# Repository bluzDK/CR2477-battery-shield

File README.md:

Bluz CR2477 Battery Shield Hardware Files
==========
Bluz is a Development Kit (DK) that implements the Wiring language and talks to the [Particle](https://www.particle.io/) cloud through Bluetooth Low Energy. It can be accessed through a REST API and programmed from a Web IDE.

The CR2477 battery shield is intended to let bluz run off the biggest, baddest coin cell battery in the land.

This shield is not produced or sold, the files are provided here as a reference or so others can create the shield themselves. The PCB can be purchased from [OSH Park directly here](https://oshpark.com/shared_projects/7VCoguxF). The BOM has all the parts listed with links to DigiKey for easy purchase. 

These files have been made available online through a [Creative Commons Attribution-ShareAlike 3.0](http://creativecommons.org/licenses/by-sa/3.0/) license.

You are welcome to distribute, remix, and use these files for commercial purposes. If you do so, please attribute the original design to Bluz both on the website and on the physical packaging of the product or in the instruction manual. All derivative works must be published under the same or a similar license.

All items are subject to change over time as the product is designed, so make sure you are always looking at the latest information by pulling often.

##Sections
<b>BOM</b>: Current Bill of Materials for the battery shield.

<b>HW Design</b>: Schematics, board layouts, and other design files.

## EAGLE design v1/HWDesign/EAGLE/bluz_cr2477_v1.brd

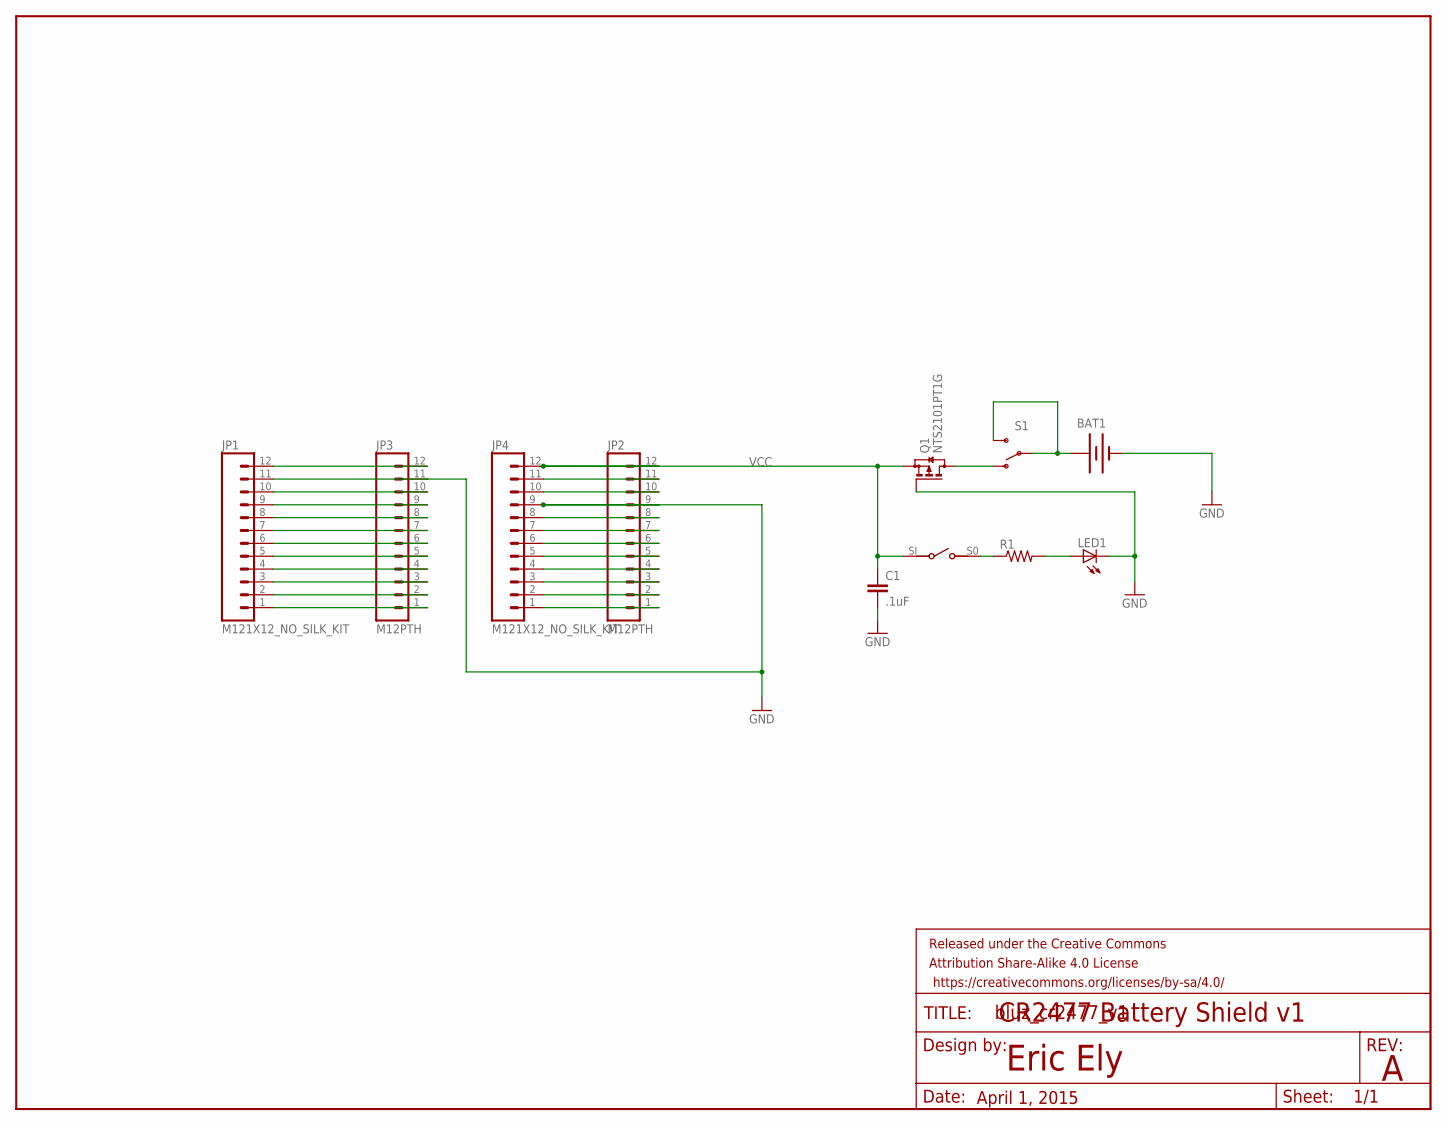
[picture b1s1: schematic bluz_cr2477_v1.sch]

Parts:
BAT1: BATTERY245PTH; BATTCON_245MM_PTH
C1: .1uF; 0603-CAP
FRAME1: FRAME-LETTER; CREATIVE_COMMONS
JP1, JP4: M121X12_NO_SILK_KIT; 1X12_NO_SILK_KIT
JP2, JP3: M12PTH; 1X12
LED1: LEDCHIPLED_0603; CHIPLED_0603
Q1: NTS2101PT1G; SOT323
R1: RESISTOR0603-RES; 0603-RES
S1: SWITCH-SPDTKIT; SWITCH-SPDT_KIT
S2: CHS-01TASMD; CHS-01TA

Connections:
GND: BAT1.2 (-), C1.2, JP1.11, JP2.9, JP3.11, JP4.9, LED1.C, Q1.1 (G)
unnamed: BAT1.3 (+), S1.2, S1.3 (S)
unnamed: JP1.1, JP3.1
unnamed: LED1.A, R1.2
unnamed: R1.1, S2.S0 (SO)
unnamed: Q1.3 (D), S1.1 (O)
unnamed: JP1.2, JP3.2
unnamed: JP1.3, JP3.3
unnamed: JP1.4, JP3.4
unnamed: JP1.5, JP3.5
unnamed: JP1.6, JP3.6
unnamed: JP1.7, JP3.7
unnamed: JP1.8, JP3.8
unnamed: JP1.9, JP3.9
unnamed: JP1.10, JP3.10
unnamed: JP1.12, JP3.12
unnamed: JP2.1, JP4.1
unnamed: JP2.2, JP4.2
unnamed: JP2.3, JP4.3
unnamed: JP2.4, JP4.4
unnamed: JP2.5, JP4.5
unnamed: JP2.6, JP4.6
unnamed: JP2.7, JP4.7
unnamed: JP2.8, JP4.8
unnamed: JP2.10, JP4.10
unnamed: JP2.11, JP4.11
VCC: C1.1, JP2.12, JP4.12, Q1.2 (S), S2.SI (S!)

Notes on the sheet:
Eric Ely
April 1, 2015
CR2477 Battery Shield v1

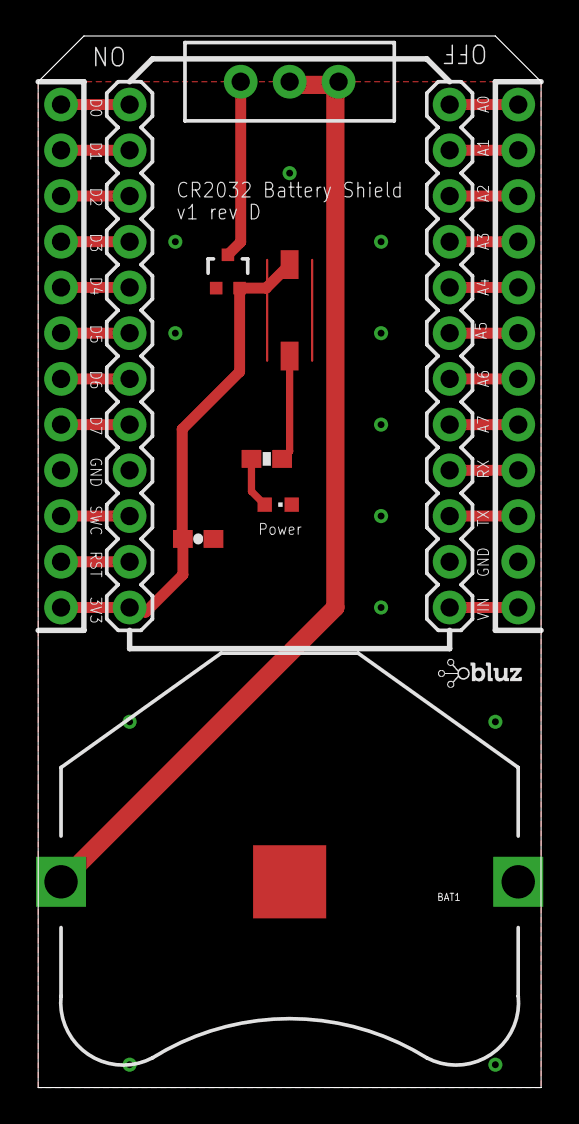
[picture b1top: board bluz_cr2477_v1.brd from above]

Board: 2 copper layers, 27.9 x 58.4 mm, 13 parts (0 on the bottom side), 27 nets.

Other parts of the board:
U$1: BLUZE_LOGO_LOW_RES

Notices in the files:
parts and their libraries:
SparkFun-Electromechanical: Licensing: Creative Commons ShareAlike 4.0 International - https://creativecommons.org/licenses/by-sa/4.0
SparkFun-Aesthetics: Released under the Creative Commons Attribution Share-Alike 4.0 License
SparkFun-Aesthetics: https://creativecommons.org/licenses/by-sa/4.0
